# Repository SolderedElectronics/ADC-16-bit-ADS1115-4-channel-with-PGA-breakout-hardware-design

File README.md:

# ADC 16-bit ADS1115 4-channel with PGA breakout Hardware Design

## About the Product

|  |
| :----------------------------------------------------------: |
| [Buy ADC 16-bit ADS1115 4-channel with PGA breakout](https://www.solde.red/333095) |

ADC (Analog Digital Converter) is a device that reads analog signals (just like the analogRead () function in Arduino IDE) and converts them into a digital signal that can be read by a microcontroller. This breakout is based on the ADS1115 ADC, which reads values in 16-bit resolution, receives a maximum of 3.3V on its inputs and has a total of 4 channels (which can also be used as two differential). Works great with each microcontroller at 5V. It has 2 easyC connectors for easier connection on I2C communication.

---

## Repository Contents

This repository contains all design files for ADC 16-bit ADS1115 4-channel with PGA breakout, organized as follows:

- **`CAD` folder**: Contains KiCAD design files, including:
  - Schematics
  - PCB layout
  - Panel PCB layout
  - Source 3D files in Fusion360, if any
  - All files are sorted by version with a detailed change log.
- **`OUTPUTS` folder**: Includes all production-ready files, such as:
  - Bill of Materials (BOM) and interactive BOM (iBOM)
  - PDF versions of schematics
  - 3D `.step` file of the board
  - 3D-printable models
  - Gerber files for PCB manufacturing
  - Image of the pinout of the board
  - Product image
  - Compliance, legal and generic sales documents

Refer to the `Change Log` in the CAD folder for details about updates between versions.

---

## Learn More About the Product

Beyond the repository, explore the following resources:

### Soldered Verify

The **Soldered Verify** system ensures every board you purchase from Soldered is fully functional. It also provides access to exclusive test data for your product. To get started, find the unique Soldered Verify ID on your product's packaging and enter the ID on the [Soldered Verify page](https://soldered.com/verify/) to access test results and additional product details.

### Soldered Community

Soldered Community is your go-to place for technical support. Our engineers track and answer all questions posted there, and it’s a great space for the maker community. Get answers to your questions and solutions for your challenges at [Soldered Community](https://soldered.com/community).

### solde.red

solde.red is an ultimate URL shortener and information hub. Access it by typing solde.red/ followed by your product SKU, e.g., [solde.red/333000](https://solde.red/333000), to find getting-started guides, datasheets, open-source hardware and software files, certifications, images, pinouts, and more. Read more about the shortener [here](https://solde.red/info/).

---

## Contributing

Contributions are welcome! Here’s how you can get involved:

- Submit pull requests to enhance the design or fix issues.
- Report bugs or problems by opening an issue.

We encourage community collaboration to make this product even better.

---

## About Soldered

[Soldered for Makers](https://soldered.com) specializes in designing and manufacturing electronic products tailored for enthusiasts, ranging from hobbyists to professionals. Our portfolio includes electronic boards, sensors, and actuators that are widely utilized in fields such as microelectronics, mechatronics, robotics, programming, and IoT. Every product we offer is designed in-house and built upon open-source hardware and software platforms. Proudly certified and manufactured within the European Union, our catalog likely includes the product you need for your project.

We complement these products with comprehensive tutorials and manuals, product descriptions, schematics, programming codes, and project examples. Our round-the-clock [customer and technical support](https://soldered.com/community) is available for all our products, irrespective of the sales channel. Soldered’s success and services reflect our maker community’s unwavering [trust](https://www.trustpilot.com/review/soldered.com), for which we are deeply grateful. Join our community and create using Soldered products.

---

## License

All Soldered open-source hardware (OSH) is under The TAPR Open Hardware License. Read more in the LICENSE file located in this repository.

**Disclaimer:**

No warranty - all designs in this repository are distributed in the hope that they will be useful, but without any warranty. They are provided "AS IS", therefore without warranty of any kind, either expressed or implied. The entire quality and performance of what you do with the contents of this repository are your responsibility. In no event Soldered Electronics will be liable for your damages, or losses, including any general, special, incidental, or consequential damage arising out of the use or inability to use the contents of this repository. 

---

## Have fun!

Thank you for your support from your fellow makers at Soldered Electronics.

Happy Making!

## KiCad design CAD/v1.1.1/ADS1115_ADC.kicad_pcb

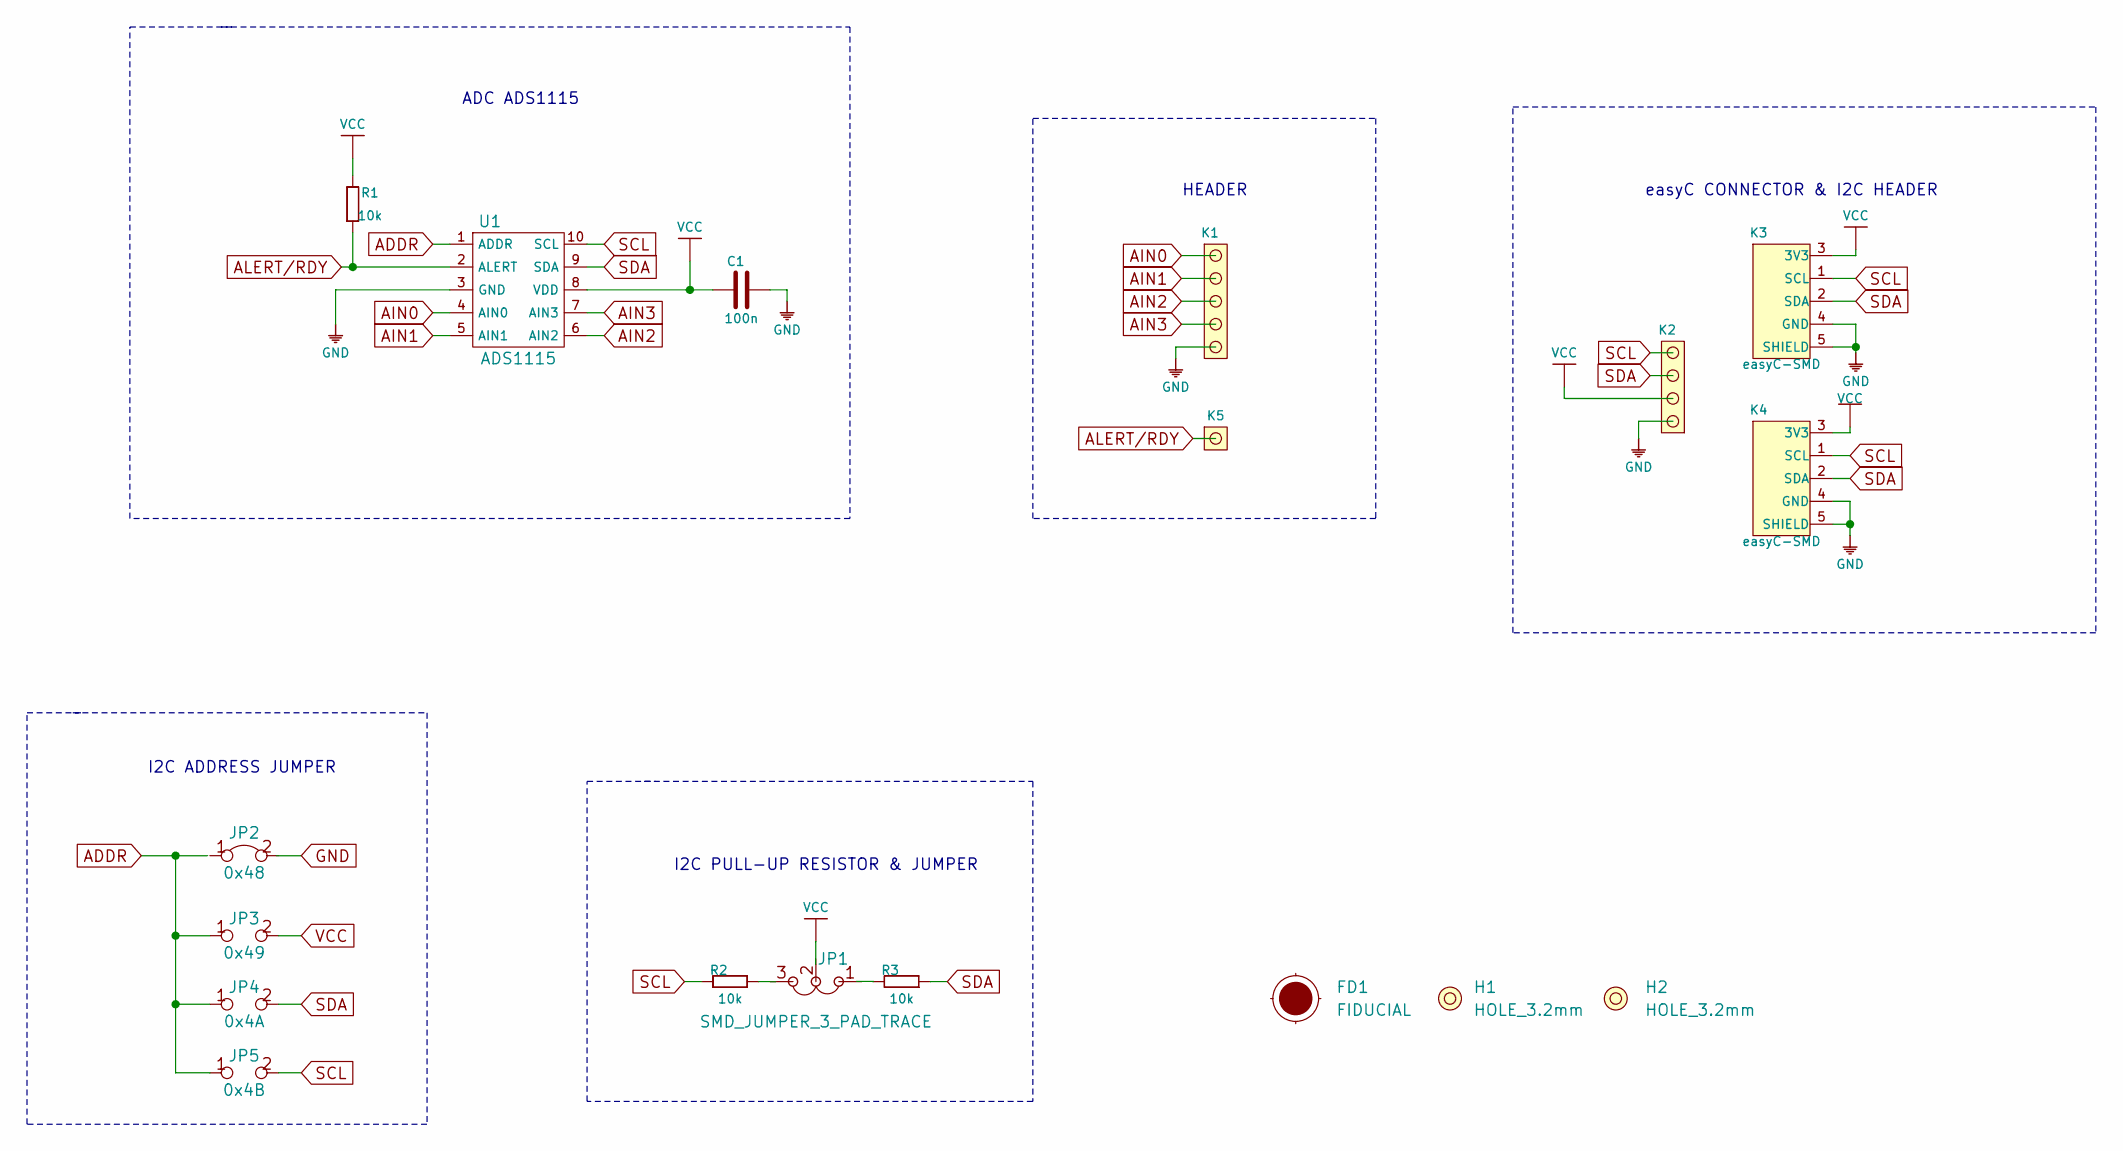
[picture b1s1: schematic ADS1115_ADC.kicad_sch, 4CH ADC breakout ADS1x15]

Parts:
C1: 100n; 0603C
FD1: FIDUCIAL; FIDUCIAL_23
H1, H2: HOLE_3.2mm
JP1: SMD_JUMPER_3_PAD_TRACE
JP2: 0x48; SMD_JUMPER_CONNECTED
JP3: 0x49; SMD_JUMPER
JP4: 0x4A; SMD_JUMPER
JP5: 0x4B; SMD_JUMPER
K1: HEADER_MALE_5X1
K2: HEADER_MALE_4X1
K3, K4: easyC-SMD; easyC-connector
K5: HEADER_MALE_1X1
R1, R2, R3: 10k; 0603R
U1: ADS1115; VSSOP

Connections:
ADDR: JP2.1, JP3.1, JP4.1, JP5.1, U1.1 (ADDR)
AIN0: K1.5, U1.4 (AIN0)
AIN1: K1.4, U1.5 (AIN1)
AIN2: K1.3, U1.6 (AIN2)
AIN3: K1.2, U1.7 (AIN3)
ALERT/RDY: K5.1, R1.1, U1.2 (ALERT)
GND: C1.2, JP2.2, K1.1, K2.1, K3.4 (GND), K3.5 (SHIELD), K4.4 (GND), K4.5 (SHIELD), U1.3 (GND)
unnamed: JP1.1, R3.2
unnamed: JP1.3, R2.1
SCL: JP5.2, K2.4, K3.1 (SCL), K4.1 (SCL), R2.2, U1.10 (SCL)
SDA: JP4.2, K2.3, K3.2 (SDA), K4.2 (SDA), R3.1, U1.9 (SDA)
VCC: C1.1, JP1.2, JP3.2, K2.2, K3.3 (3V3), K4.3 (3V3), R1.2, U1.8 (VDD)

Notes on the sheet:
HEADER
I2C ADDRESS JUMPER
I2C PULL-UP RESISTOR & JUMPER
ADC ADS1115
easyC CONNECTOR & I2C HEADER

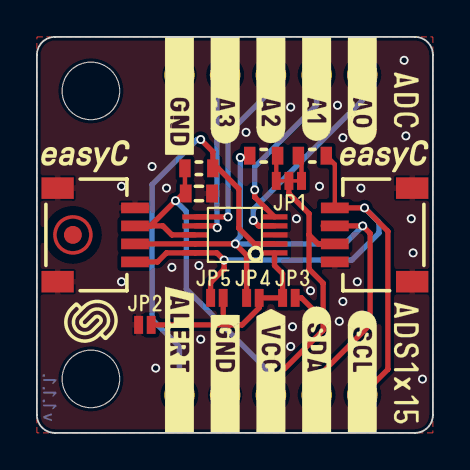
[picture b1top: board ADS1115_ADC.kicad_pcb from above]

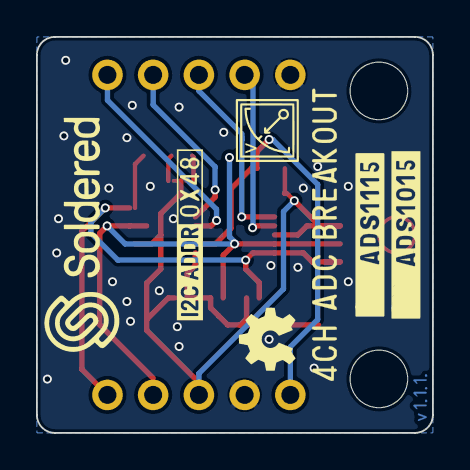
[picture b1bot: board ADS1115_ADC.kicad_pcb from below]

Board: 2 copper layers, 22.0 x 22.0 mm, 18 parts (3 on the bottom side), 12 nets.

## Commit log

2022-08-06 Updating open source files.
